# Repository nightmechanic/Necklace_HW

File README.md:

Necklace_HW
===========

This repository contains the HW for Gali's Necklace project.
It is a Kicad project

Copyright Nightmechanic 2014

<br /><span xmlns:dct="http://purl.org/dc/terms/" property="dct:title">Gali's necklace</span> by <span xmlns:cc="http://creativecommons.org/ns#" property="cc:attributionName">Nightmechanic (Ran Katz)</span> is licensed under a <a rel="license" href="http://creativecommons.org/licenses/by-sa/4.0/">Creative Commons Attribution-ShareAlike 4.0 International License</a>.<br />Based on a work at <a xmlns:dct="http://purl.org/dc/terms/" href="https://github.com/nightmechanic/Necklace_HW/" rel="dct:source">https://github.com/nightmechanic/Necklace_HW/</a>.

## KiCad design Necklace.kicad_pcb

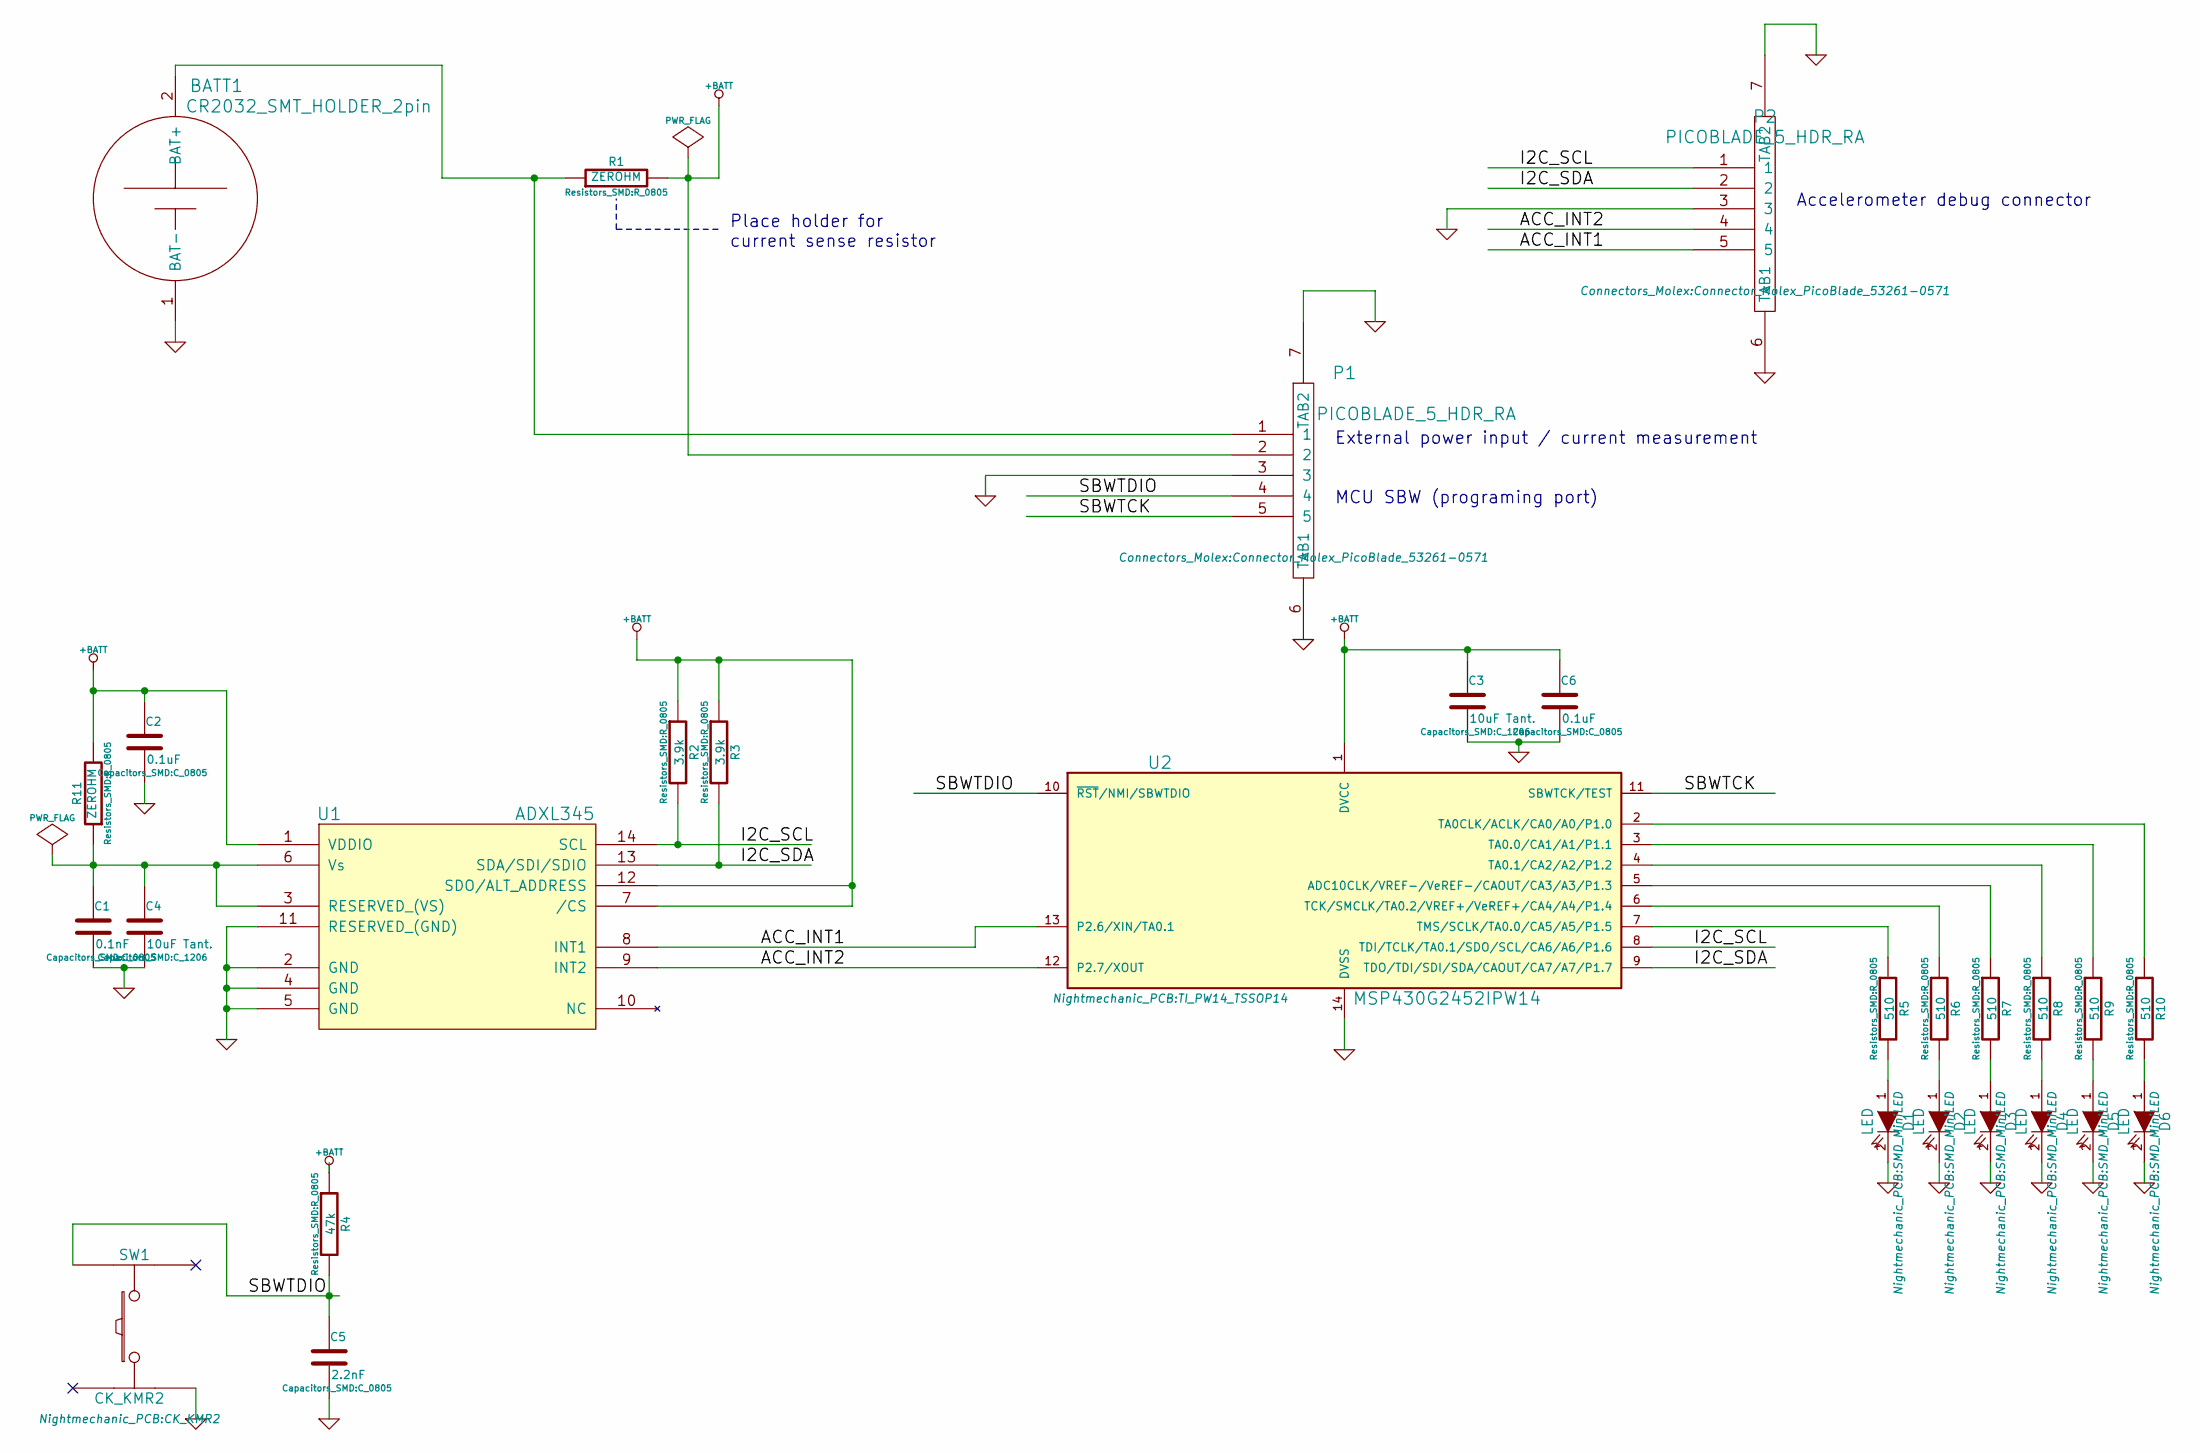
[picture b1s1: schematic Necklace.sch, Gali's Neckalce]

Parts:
BATT1: CR2032_SMT_HOLDER_2pin; SMTU_2032
C1: 0.1nF; C_0805
C2, C6: 0.1uF; C_0805
C3, C4: 10uF Tant.; C_1206
C5: 2.2nF; C_0805
D1, D2, D3, D4, D5, D6: LED; SMD_MiniLED
P1, P2: PICOBLADE_5_HDR_RA; Connector_Molex_PicoBlade_53261-0571
R1, R11: ZEROHM; R_0805
R2, R3: 3.9k; R_0805
R4: 47k; R_0805
R5, R6, R7, R8, R9, R10: 510; R_0805
SW1: CK_KMR2
U1: ADXL345; AD_LGA14
U2: MSP430G2452IPW14; TI_PW14_TSSOP14

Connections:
+BATT: C2.1, C3.1, C6.1, P1.2, R1.2, R2.1, R3.1, R4.1, R11.2, U1.1 (VDDIO), U1.7 (/CS), U1.12 (SDO/ALT_ADDRESS), U2.1 (DVCC)
/ACC_INT1: P2.5, U1.8 (INT1), U2.13 (P2.6/XIN/TA0.1)
/ACC_INT2: P2.4, U1.9 (INT2), U2.12 (P2.7/XOUT)
/ADC_VS: C1.1, C4.1, R11.1, U1.3 (RESERVED_(VS)), U1.6 (Vs)
/I2C_SCL: P2.1, R2.2, U1.14 (SCL), U2.8 (TDI/TCLK/TA0.1/SDO/SCL/CA6/A6/P1.6)
/I2C_SDA: P2.2, R3.2, U1.13 (SDA/SDI/SDIO), U2.9 (TDO/TDI/SDI/SDA/CAOUT/CA7/A7/P1.7)
/MCU_LED1: R10.1, U2.2 (TA0CLK/ACLK/CA0/A0/P1.0)
/MCU_LED2: R9.1, U2.3 (TA0.0/CA1/A1/P1.1)
/MCU_LED3: R8.1, U2.4 (TA0.1/CA2/A2/P1.2)
/MCU_LED4: R7.1, U2.5 (ADC10CLK/VREF-/VeREF-/CAOUT/CA3/A3/P1.3)
/MCU_LED5: R6.1, U2.6 (TCK/SMCLK/TA0.2/VREF+/VeREF+/CA4/A4/P1.4)
/MCU_LED6: R5.1, U2.7 (TMS/SCLK/TA0.0/CA5/A5/P1.5)
/SBWTCK: P1.5, U2.11 (SBWTCK/TEST)
/SBWTDIO: C5.1, P1.4, R4.2, SW1.1, U2.10 (~RST~/NMI/SBWTDIO)
/V_BATT: BATT1.2 (BAT+), P1.1, R1.1
GND: BATT1.1 (BAT-), C1.2, C2.2, C3.2, C4.2, C5.2, C6.2, D1.2 (K), D2.2 (K), D3.2 (K), D4.2 (K), D5.2 (K), D6.2 (K), P1.3, P1.6 (TAB1), P1.7 (TAB2), P2.3, P2.6 (TAB1), P2.7 (TAB2), SW1.4, U1.2 (GND), U1.4 (GND), U1.5 (GND), U1.11 (RESERVED_(GND)), U2.14 (DVSS)
unnamed: D1.1 (A), R5.2
unnamed: D2.1 (A), R6.2
unnamed: D3.1 (A), R7.2
unnamed: D4.1 (A), R8.2
unnamed: D5.1 (A), R9.2
unnamed: D6.1 (A), R10.2

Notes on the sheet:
Place holder for current sense resistor
External power input / current measurement MCU SBW (programing port)
Accelerometer debug connector

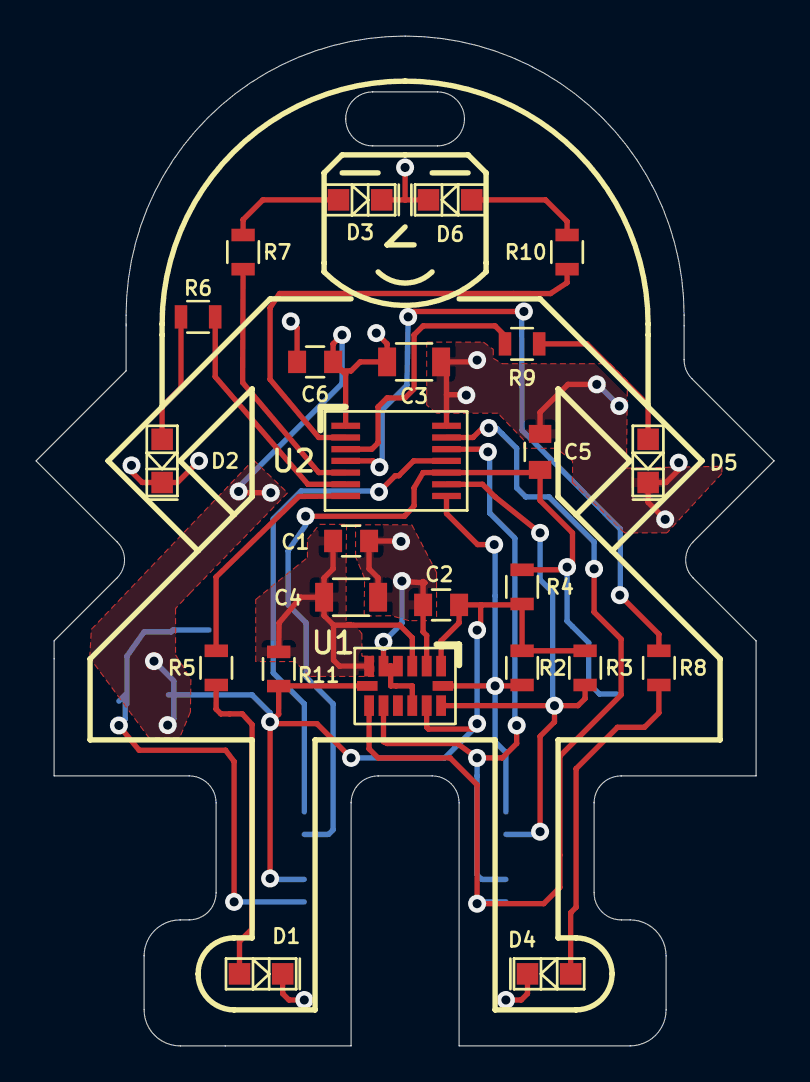
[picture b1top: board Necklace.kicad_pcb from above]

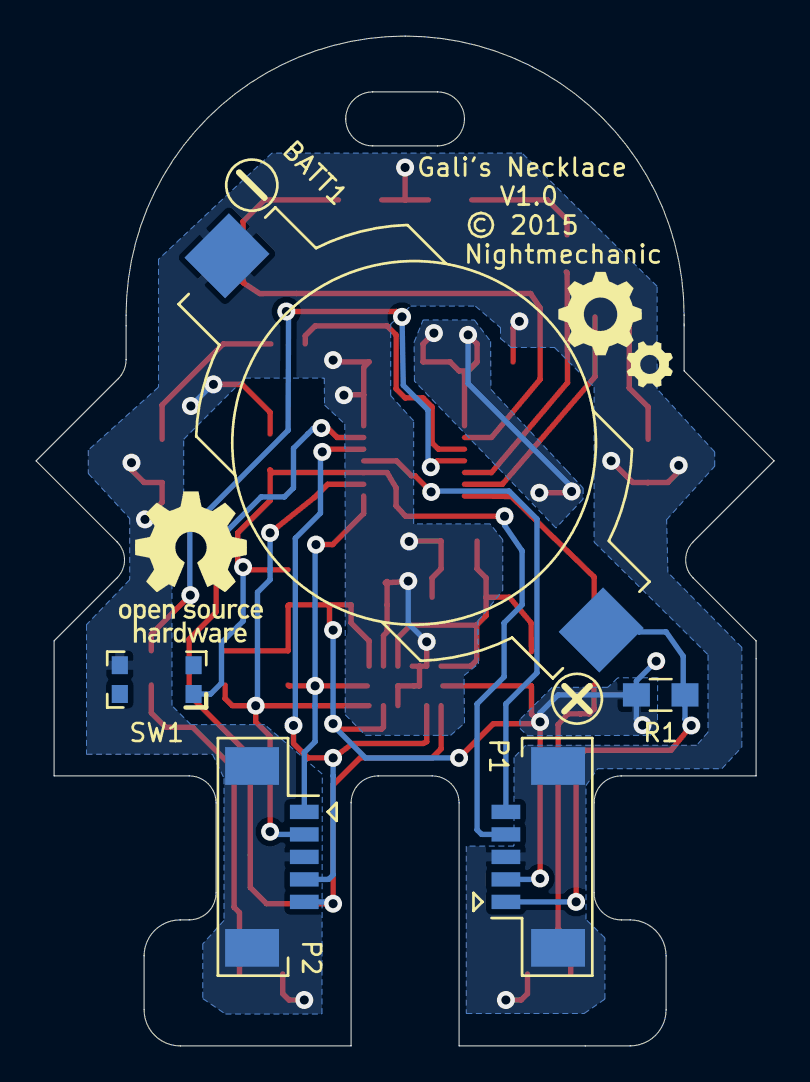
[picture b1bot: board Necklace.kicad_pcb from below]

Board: 2 copper layers, 41.0 x 56.1 mm, 31 parts (7 on the bottom side), 22 nets.

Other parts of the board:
VAL: REF; Gears_F.SilkS_8mm
VAL#2: REF; OSHW_F.SilkS_8mm

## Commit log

2014-06-24 First version
2015-01-21 started layout
2015-01-22 layout continues
2015-01-29 and some more layout
2015-01-29 late night layout...
2015-02-01 finished layout, hopeflly
2015-02-02 V1.0 ready to fab

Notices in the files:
Necklace.kicad_pcb:
© 2015
Necklace.sch:
Copyright by Nightmechanic 2014
Open source under the Creative Commons Attribution 4.0 license
http://creativecommons.org/licenses/by/4.0
